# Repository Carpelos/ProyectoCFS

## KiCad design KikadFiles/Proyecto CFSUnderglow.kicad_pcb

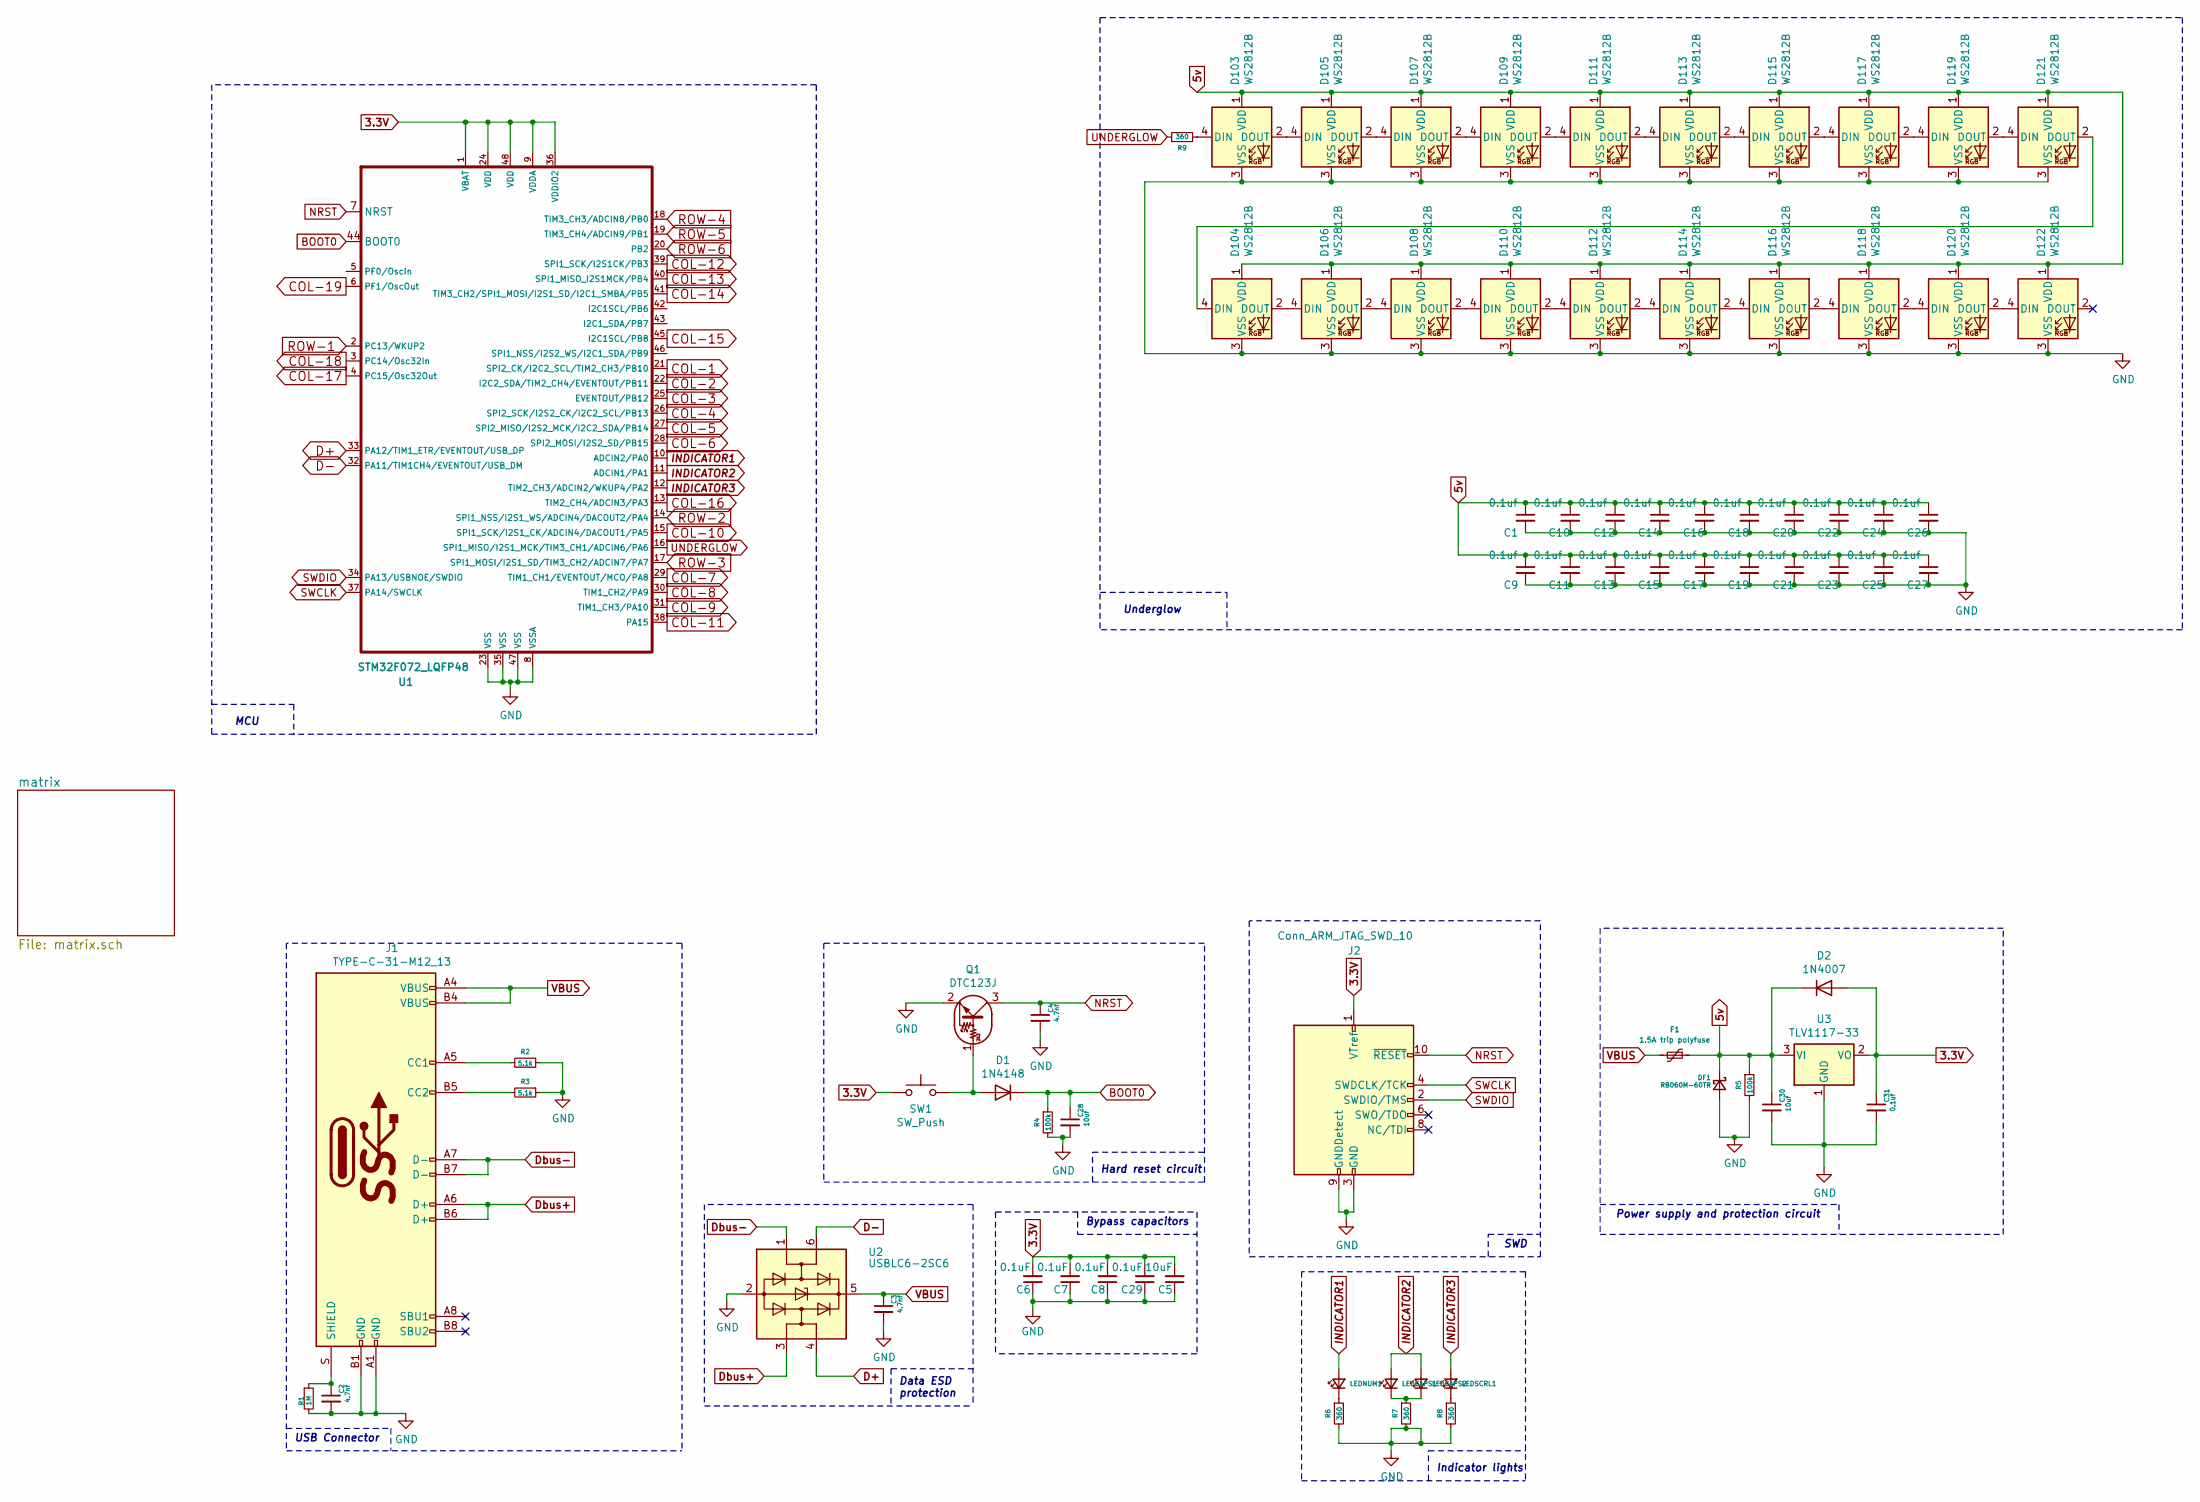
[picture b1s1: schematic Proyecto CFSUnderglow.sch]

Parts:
C1, C9, C10, C11, C12, C13, C14, C15, C16, C17, C18, C19, C20, C21, C22, C23, C24, C25, C26, C27, C31: 0.1uf; C_0805_2012Metric_Pad1.15x1.40mm_HandSolder
C2, C3, C4: 4.7nf; C_0805_2012Metric_Pad1.15x1.40mm_HandSolder
C5: 10uF; C_0805_2012Metric_Pad1.15x1.40mm_HandSolder
C6, C7, C8, C29: 0.1uF; C_0805_2012Metric_Pad1.15x1.40mm_HandSolder
C28, C30: 10uf; C_0805_2012Metric_Pad1.15x1.40mm_HandSolder
D1: 1N4148; D_SOD-123
D2: 1N4007; D_SOD-123
D103, D104, D105, D106, D107, D108, D109, D110, D111, D112, D113, D114, D115, D116, D117, D118, D119, D120, D121, D122: WS2812B; LED_WS2812B_PLCC4_5.0x5.0mm_P3.2mm
DF1: RB060M-60TR; D_SOD-123
F1: 1.5A trip polyfuse; Fuse_1812_4532Metric_Pad1.30x3.40mm_HandSolder
J1: TYPE-C-31-M12_13; TYPE-C-31-M-12
J2: Conn_ARM_JTAG_SWD_10; PinHeader_2x05_P2.54mm_Vertical
LEDCAPS1, LEDCAPS2: L; LED_D1.8mm_W3.3mm_H2.4mm
LEDNUM1: L; LED_D1.8mm_W3.3mm_H2.4mm
LEDSCRL1: L; LED_D1.8mm_W3.3mm_H2.4mm
Q1: DTC123J; SOT-23
R1: 1M; R_0805_2012Metric_Pad1.15x1.40mm_HandSolder
R2, R3: 5.1k; R_0805_2012Metric_Pad1.15x1.40mm_HandSolder
R4, R5: 100k; R_0805_2012Metric_Pad1.15x1.40mm_HandSolder
R6, R7, R8, R9: 360; R_0805_2012Metric_Pad1.15x1.40mm_HandSolder
SW1: SW_Push; smdPushBtn
U1: STM32F072_LQFP48; LQFP-48_7x7mm_P0.5mm
U2: USBLC6-2SC6; SOT-23-6
U3: TLV1117-33; SOT-223-3_TabPin2

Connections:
3.3V: C5.2, C6.2, C7.2, C8.2, C29.2, C31.1, D2.2 (A), J2.1 (VTref), SW1.1, U1.1 (VBAT), U1.9 (VDDA), U1.24 (VDD), U1.36 (VDDIO2), U1.48 (VDD), U3.2 (VO)
5v: C1.1, C9.1, C10.1, C11.1, C12.1, C13.1, C14.1, C15.1, C16.1, C17.1, C18.1, C19.1, C20.1, C21.1, C22.1, C23.1, C24.1, C25.1, C26.1, C27.1, C30.1, D2.1 (K), D103.1 (VDD), D104.1 (VDD), D105.1 (VDD), D106.1 (VDD), D107.1 (VDD), D108.1 (VDD), D109.1 (VDD), D110.1 (VDD), D111.1 (VDD), D112.1 (VDD), D113.1 (VDD), D114.1 (VDD), D115.1 (VDD), D116.1 (VDD), D117.1 (VDD), D118.1 (VDD), D119.1 (VDD), D120.1 (VDD), D121.1 (VDD), D122.1 (VDD), DF1.1 (K), F1.1, R5.1, U3.3 (VI)
BOOT0: C28.1, D1.1 (K), R4.1, U1.44 (BOOT0)
COL-1: U1.21 (SPI2_CK/I2C2_SCL/TIM2_CH3/PB10); also elsewhere on the board
COL-2: U1.22 (I2C2_SDA/TIM2_CH4/EVENTOUT/PB11); also elsewhere on the board
COL-3: U1.25 (EVENTOUT/PB12); also elsewhere on the board
COL-4: U1.26 (SPI2_SCK/I2S2_CK/I2C2_SCL/PB13); also elsewhere on the board
COL-5: U1.27 (SPI2_MISO/I2S2_MCK/I2C2_SDA/PB14); also elsewhere on the board
COL-6: U1.28 (SPI2_MOSI/I2S2_SD/PB15); also elsewhere on the board
COL-7: U1.29 (TIM1_CH1/EVENTOUT/MCO/PA8); also elsewhere on the board
COL-8: U1.30 (TIM1_CH2/PA9); also elsewhere on the board
COL-9: U1.31 (TIM1_CH3/PA10); also elsewhere on the board
COL-10: U1.15 (SPI1_SCK/I2S1_CK/ADCIN4/DACOUT1/PA5); also elsewhere on the board
COL-11: U1.38 (PA15); also elsewhere on the board
COL-12: U1.39 (SPI1_SCK/I2S1CK/PB3); also elsewhere on the board
COL-13: U1.40 (SPI1_MISO_I2S1MCK/PB4); also elsewhere on the board
COL-14: U1.41 (TIM3_CH2/SPI1_MOSI/I2S1_SD/I2C1_SMBA/PB5); also elsewhere on the board
COL-15: U1.45 (I2C1SCL/PB8); also elsewhere on the board
COL-16: U1.13 (TIM2_CH4/ADCIN3/PA3); also elsewhere on the board
COL-17: U1.4 (PC15/Osc32Out); also elsewhere on the board
COL-18: U1.3 (PC14/Osc32In); also elsewhere on the board
COL-19: U1.6 (PF1/OscOut); also elsewhere on the board
D+: U1.33 (PA12/TIM1_ETR/EVENTOUT/USB_DP), U2.4 (I/O2)
D-: U1.32 (PA11/TIM1CH4/EVENTOUT/USB_DM), U2.6 (I/O1)
Dbus+: J1.A6 (D+), J1.B6 (D+), U2.3 (I/O2)
Dbus-: J1.A7 (D-), J1.B7 (D-), U2.1 (I/O1)
GND: C1.2, C2.2, C3.2, C4.2, C5.1, C6.1, C7.1, C8.1, C9.2, C10.2, C11.2, C12.2, C13.2, C14.2, C15.2, C16.2, C17.2, C18.2, C19.2, C20.2, C21.2, C22.2, C23.2, C24.2, C25.2, C26.2, C27.2, C28.2, C29.1, C30.2, C31.2, D103.3 (VSS), D104.3 (VSS), D105.3 (VSS), D106.3 (VSS), D107.3 (VSS), D108.3 (VSS), D109.3 (VSS), D110.3 (VSS), D111.3 (VSS), D112.3 (VSS), D113.3 (VSS), D114.3 (VSS), D115.3 (VSS), D116.3 (VSS), D117.3 (VSS), D118.3 (VSS), D119.3 (VSS), D120.3 (VSS), D121.3 (VSS), D122.3 (VSS), DF1.2 (A), J1.A1 (GND), J1.B1 (GND), J2.3 (GND), J2.5 (GND), J2.9 (GNDDetect), Q1.2 (E), R1.2, R2.1, R3.1, R4.2, R5.2, R6.2, R7.2, R8.2, U1.8 (VSSA), U1.23 (VSS), U1.35 (VSS), U1.47 (VSS), U2.2 (GND), U3.1 (GND)
INDICATOR1: LEDNUM1.2 (A), U1.10 (ADCIN2/PA0)
INDICATOR2: LEDCAPS1.2 (A), LEDCAPS2.2 (A), U1.11 (ADCIN1/PA1)
INDICATOR3: LEDSCRL1.2 (A), U1.12 (TIM2_CH3/ADCIN2/WKUP4/PA2)
NRST: C4.1, J2.10 (~RESET~), Q1.3 (C), U1.7 (NRST)
unnamed: C2.1, J1.S (SHIELD), R1.1
unnamed: D1.2 (A), Q1.1 (B), SW1.2
unnamed: D103.2 (DOUT), D105.4 (DIN)
unnamed: D103.4 (DIN), R9.2
unnamed: D104.2 (DOUT), D106.4 (DIN)
unnamed: D104.4 (DIN), D121.2 (DOUT)
unnamed: D105.2 (DOUT), D107.4 (DIN)
unnamed: D106.2 (DOUT), D108.4 (DIN)
unnamed: D107.2 (DOUT), D109.4 (DIN)
unnamed: D108.2 (DOUT), D110.4 (DIN)
unnamed: D109.2 (DOUT), D111.4 (DIN)
unnamed: D110.2 (DOUT), D112.4 (DIN)
unnamed: D111.2 (DOUT), D113.4 (DIN)
unnamed: D112.2 (DOUT), D114.4 (DIN)
unnamed: D113.2 (DOUT), D115.4 (DIN)
unnamed: D114.2 (DOUT), D116.4 (DIN)
unnamed: D115.2 (DOUT), D117.4 (DIN)
unnamed: D116.2 (DOUT), D118.4 (DIN)
unnamed: D117.2 (DOUT), D119.4 (DIN)
unnamed: D118.2 (DOUT), D120.4 (DIN)
unnamed: D119.2 (DOUT), D121.4 (DIN)
unnamed: D120.2 (DOUT), D122.4 (DIN)
unnamed: J1.A5 (CC1), R2.2
unnamed: J1.B5 (CC2), R3.2
unnamed: LEDCAPS1.1 (K), LEDCAPS2.1 (K), R7.1
unnamed: LEDNUM1.1 (K), R6.1
unnamed: LEDSCRL1.1 (K), R8.1
ROW-1: U1.2 (PC13/WKUP2); also elsewhere on the board
ROW-2: U1.14 (SPI1_NSS/I2S1_WS/ADCIN4/DACOUT2/PA4); also elsewhere on the board
ROW-3: U1.17 (SPI1_MOSI/I2S1_SD/TIM3_CH2/ADCIN7/PA7); also elsewhere on the board
ROW-4: U1.18 (TIM3_CH3/ADCIN8/PB0); also elsewhere on the board
ROW-5: U1.19 (TIM3_CH4/ADCIN9/PB1); also elsewhere on the board
ROW-6: U1.20 (PB2); also elsewhere on the board
SWCLK: J2.4 (SWDCLK/TCK), U1.37 (PA14/SWCLK)
SWDIO: J2.2 (SWDIO/TMS), U1.34 (PA13/USBNOE/SWDIO)
UNDERGLOW: R9.1, U1.16 (SPI1_MISO/I2S1_MCK/TIM3_CH1/ADCIN6/PA6)
VBUS: C3.1, F1.2, J1.A4 (VBUS), J1.B4 (VBUS), U2.5 (VBUS)

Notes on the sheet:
USB Connector
Data ESD protection
Hard reset circuit
SWD
Bypass capacitors
Indicator lights
Power supply and protection circuit
Underglow
MCU

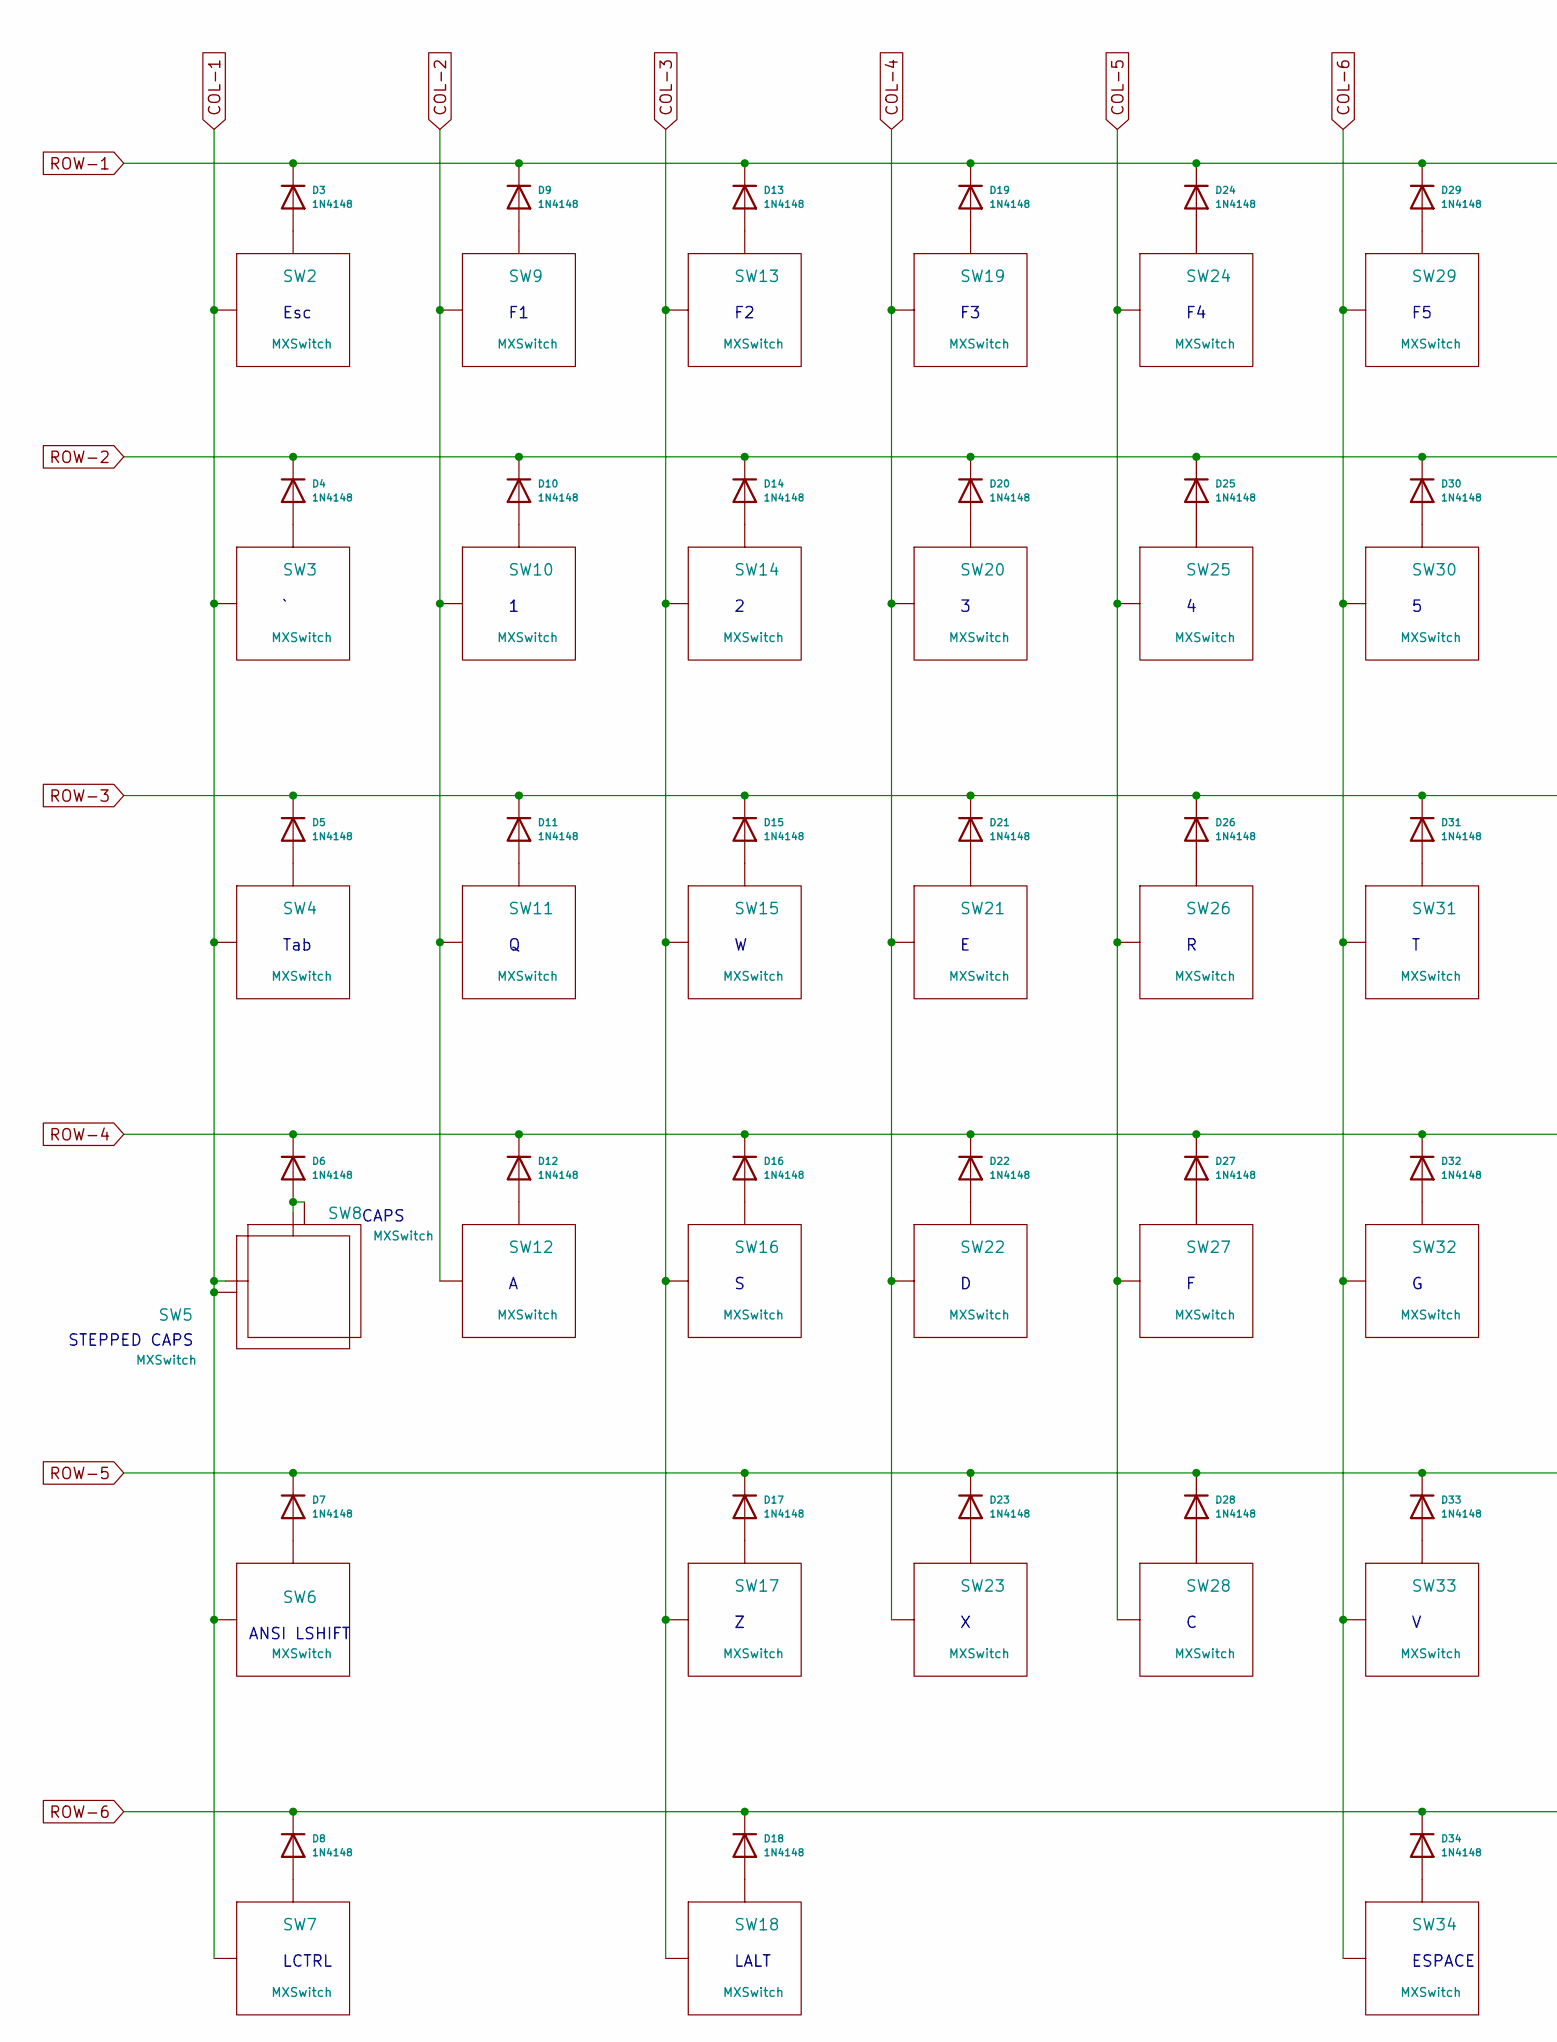
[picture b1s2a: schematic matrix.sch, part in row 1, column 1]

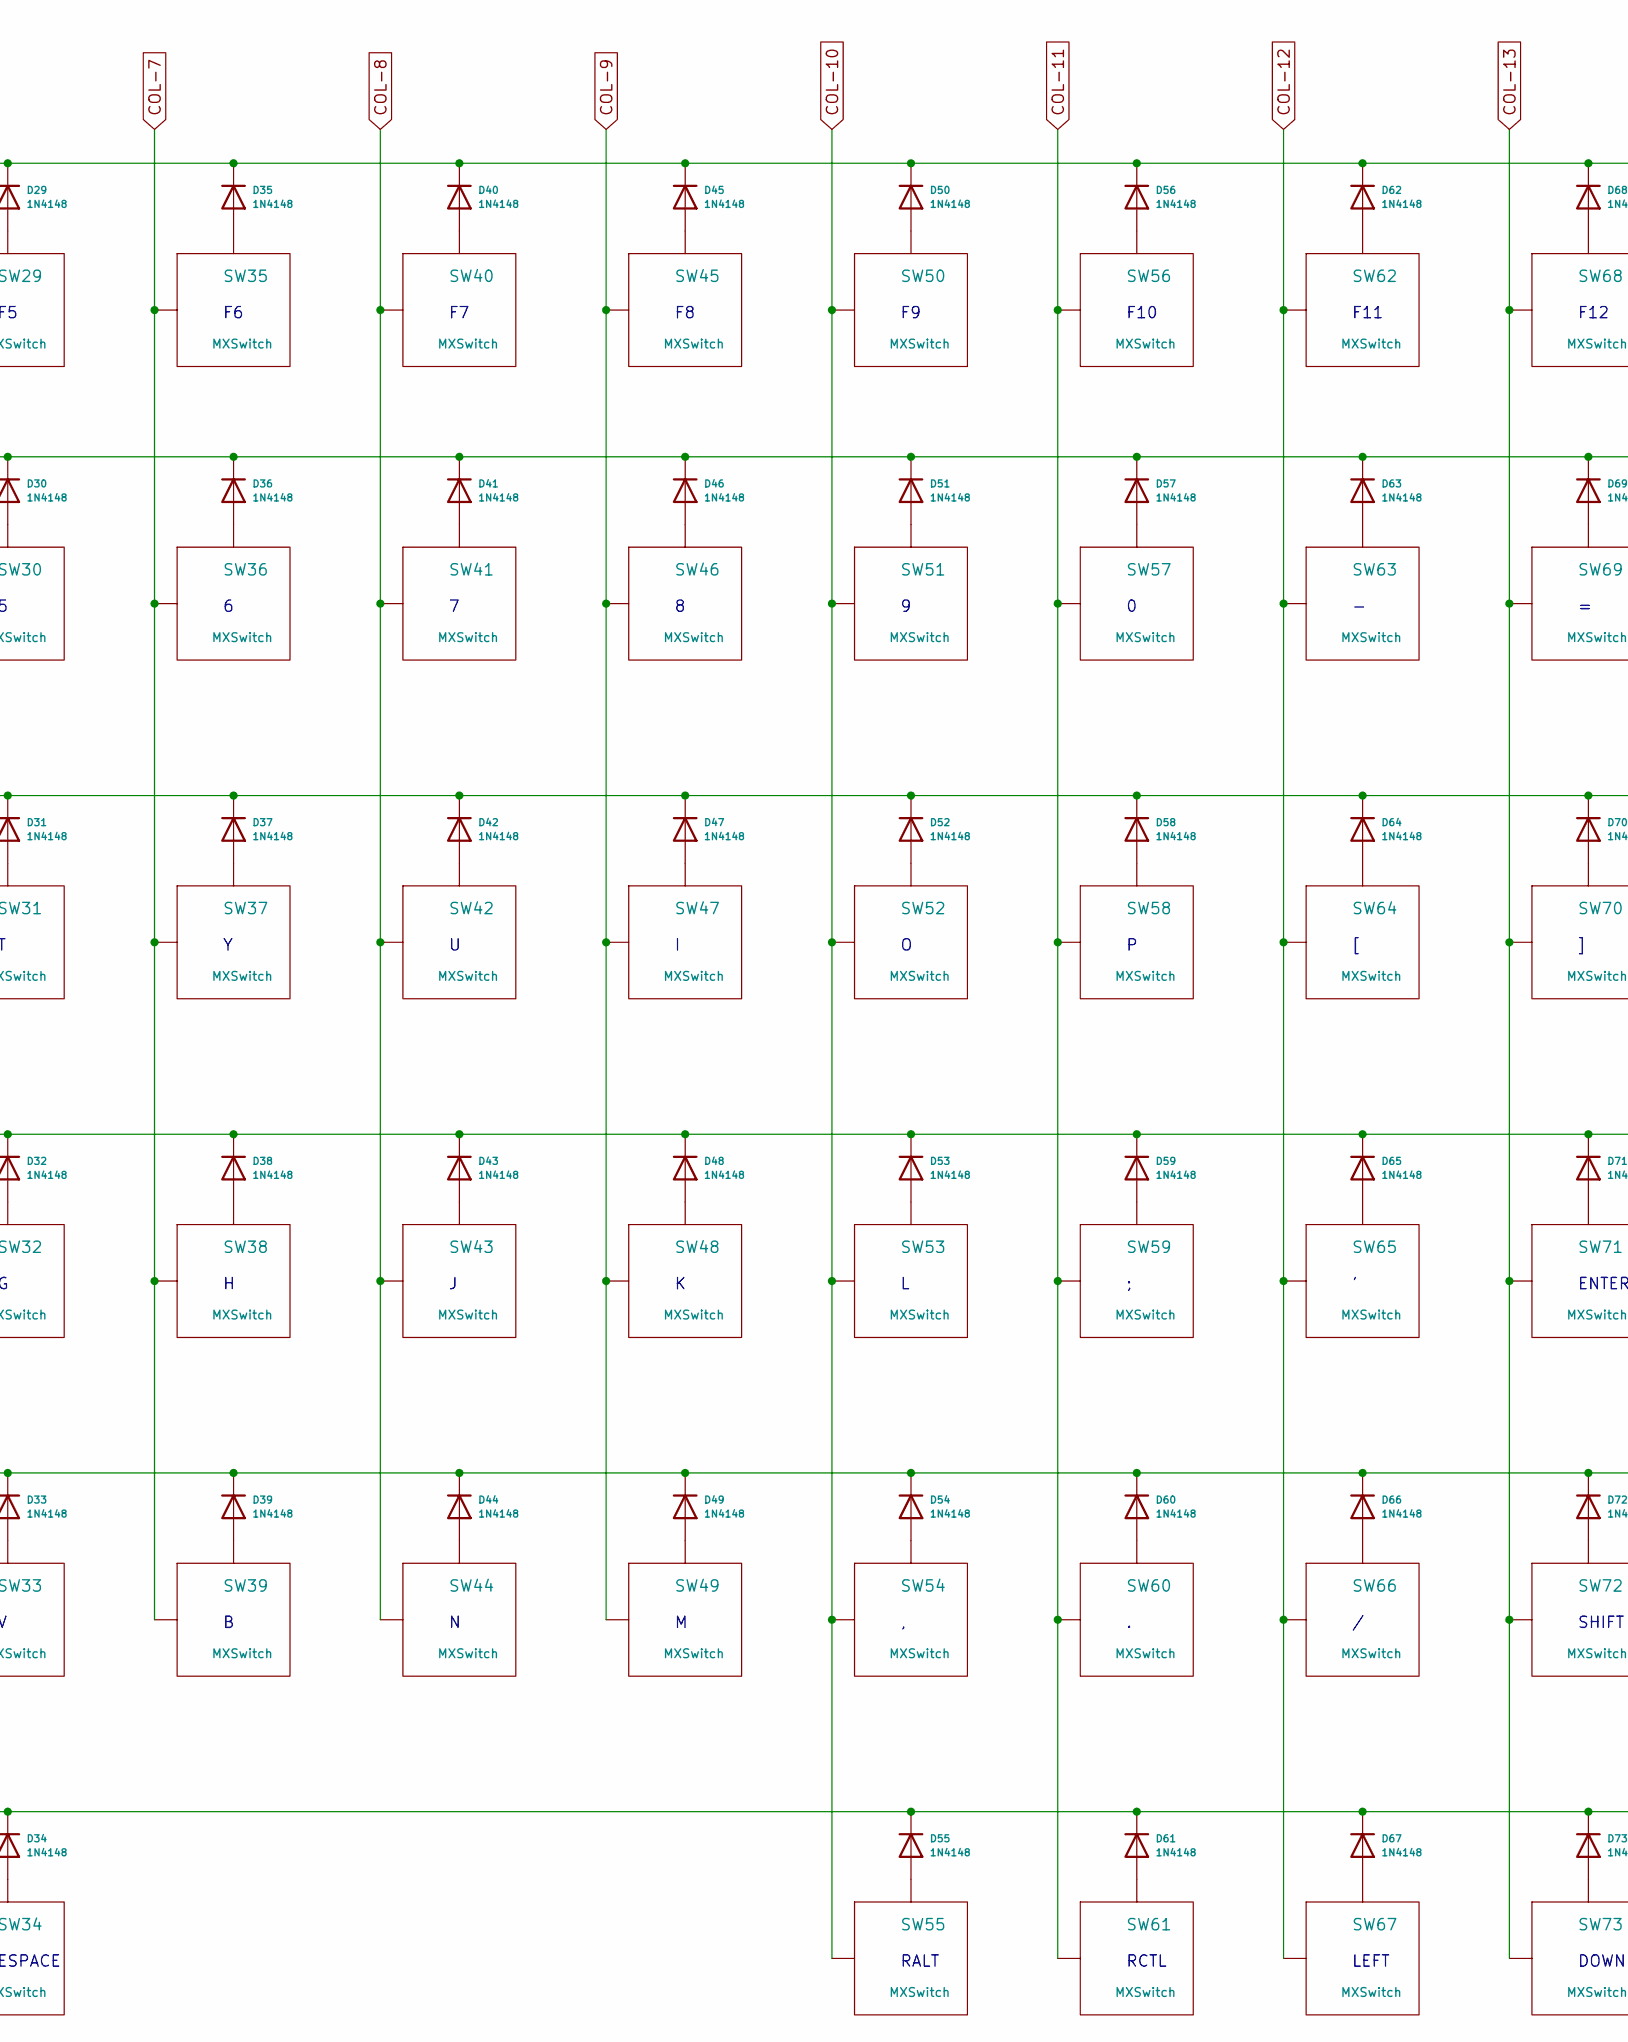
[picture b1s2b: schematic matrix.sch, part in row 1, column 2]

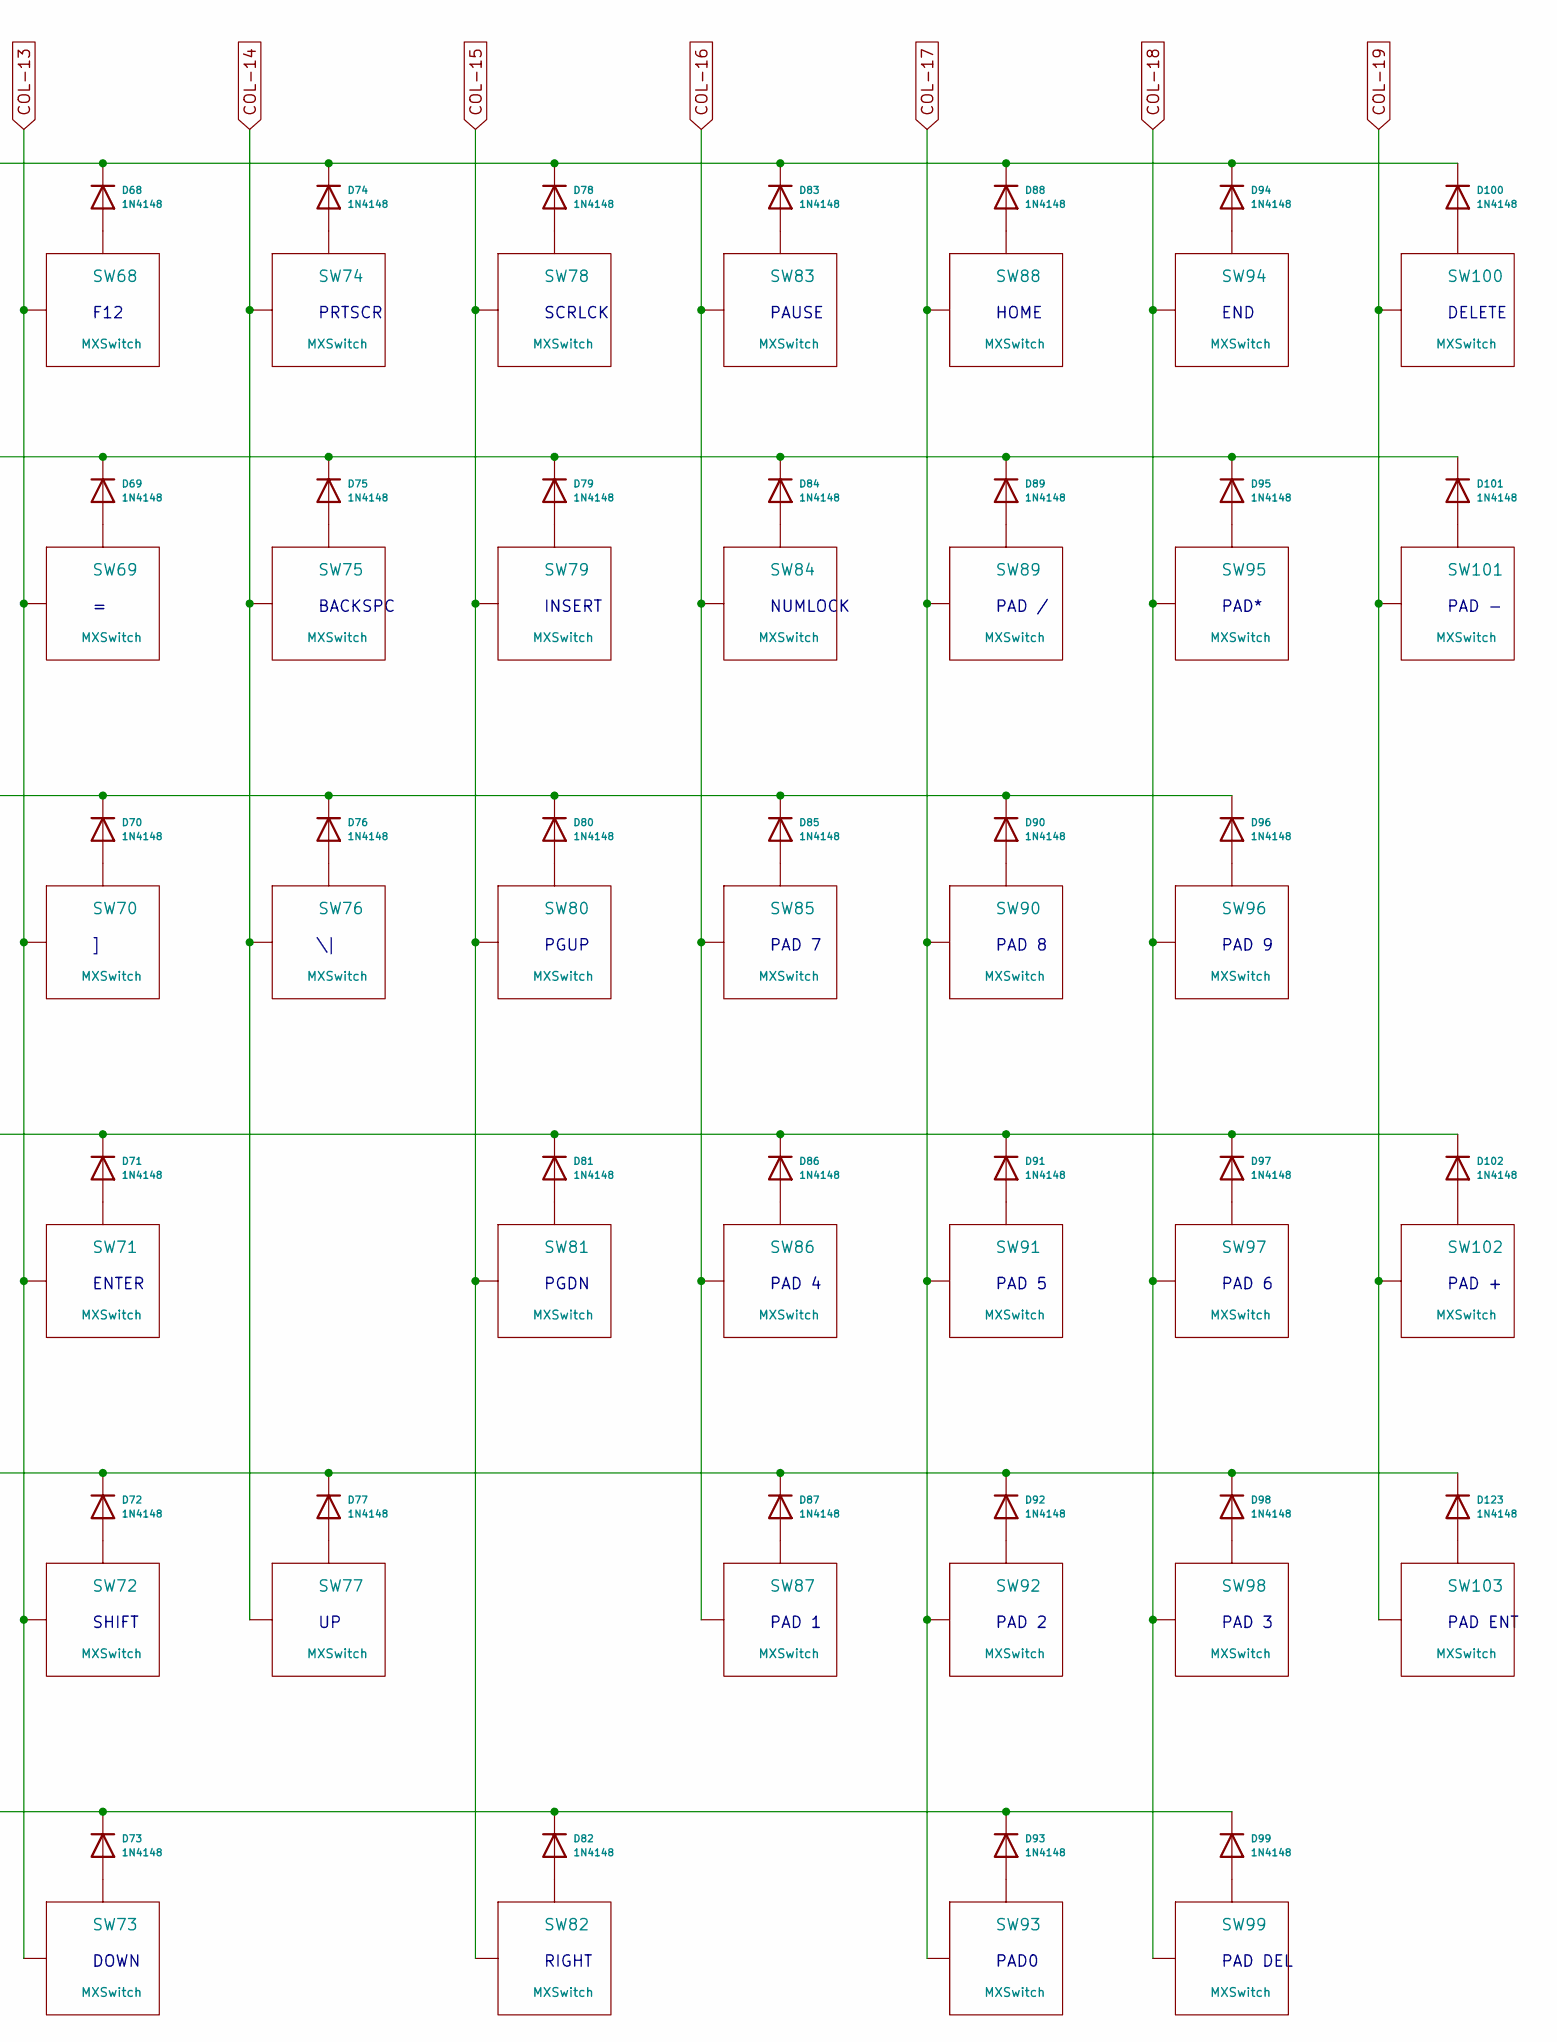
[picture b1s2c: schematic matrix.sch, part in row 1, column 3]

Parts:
D3, D4, D5, D6, D7, D8, D9, D10, D11, D12, D13, D14, D15, D16, D17, D18, D19, D20, D21, D22, D23, D24, D25, D26, D27, D28, D29, D30, D31, D32, D33, D34, D35, D36, D37, D38, D39, D40, D41, D42, D43, D44, D45, D46, D47, D48, D49, D50, D51, D52, D53, D54, D55, D56, D57, D58, D59, D60, D61, D62, D63, D64, D65, D66, D67, D68, D69, D70, D71, D72, D73, D74, D75, D76, D77, D78, D79, D80, D81, D82, D83, D84, D85, D86, D87, D88, D89, D90, D91, D92, D93, D94, D95, D96, D97, D98, D99, D100, D101, D102, D123: 1N4148; D_SOD-123
SW2, SW3, SW9, SW10, SW11, SW12, SW13, SW14, SW15, SW16, SW17, SW19, SW20, SW21, SW22, SW23, SW24, SW25, SW26, SW27, SW28, SW29, SW30, SW31, SW32, SW33, SW35, SW36, SW37, SW38, SW39, SW40, SW41, SW42, SW43, SW44, SW45, SW46, SW47, SW48, SW49, SW50, SW51, SW52, SW53, SW54, SW56, SW57, SW58, SW59, SW60, SW62, SW63, SW64, SW65, SW66, SW67, SW68, SW69, SW70, SW73, SW74, SW77, SW78, SW79, SW80, SW81, SW82, SW83, SW84, SW85, SW86, SW87, SW88, SW89, SW90, SW91, SW92, SW94, SW95, SW96, SW97, SW98, SW99, SW100, SW101: MXSwitch; MXOnly-1U-NoLED
SW4, SW7, SW18, SW55, SW61, SW76: MXSwitch; MXOnly-1.5U-NoLED
SW5: MXSwitch; MXOnly-1.25U-NoLED
SW6, SW71: MXSwitch; MXOnly-2.25U-NoLED
SW8, SW72: MXSwitch; MXOnly-1.75U-NoLED
SW34: MXSwitch; MXOnly-7U-NoLED
SW75, SW93, SW102, SW103: MXSwitch; MXOnly-2U-NoLED

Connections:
COL-1: SW2.1 (Col), SW3.1 (Col), SW4.1 (Col), SW5.1 (Col), SW6.1 (Col), SW7.1 (Col), SW8.1 (Col); also elsewhere on the board
COL-2: SW9.1 (Col), SW10.1 (Col), SW11.1 (Col), SW12.1 (Col); also elsewhere on the board
COL-3: SW13.1 (Col), SW14.1 (Col), SW15.1 (Col), SW16.1 (Col), SW17.1 (Col), SW18.1 (Col); also elsewhere on the board
COL-4: SW19.1 (Col), SW20.1 (Col), SW21.1 (Col), SW22.1 (Col), SW23.1 (Col); also elsewhere on the board
COL-5: SW24.1 (Col), SW25.1 (Col), SW26.1 (Col), SW27.1 (Col), SW28.1 (Col); also elsewhere on the board
COL-6: SW29.1 (Col), SW30.1 (Col), SW31.1 (Col), SW32.1 (Col), SW33.1 (Col), SW34.1 (Col); also elsewhere on the board
COL-7: SW35.1 (Col), SW36.1 (Col), SW37.1 (Col), SW38.1 (Col), SW39.1 (Col); also elsewhere on the board
COL-8: SW40.1 (Col), SW41.1 (Col), SW42.1 (Col), SW43.1 (Col), SW44.1 (Col); also elsewhere on the board
COL-9: SW45.1 (Col), SW46.1 (Col), SW47.1 (Col), SW48.1 (Col), SW49.1 (Col); also elsewhere on the board
COL-10: SW50.1 (Col), SW51.1 (Col), SW52.1 (Col), SW53.1 (Col), SW54.1 (Col), SW55.1 (Col); also elsewhere on the board
COL-11: SW56.1 (Col), SW57.1 (Col), SW58.1 (Col), SW59.1 (Col), SW60.1 (Col), SW61.1 (Col); also elsewhere on the board
COL-12: SW62.1 (Col), SW63.1 (Col), SW64.1 (Col), SW65.1 (Col), SW66.1 (Col), SW67.1 (Col); also elsewhere on the board
COL-13: SW68.1 (Col), SW69.1 (Col), SW70.1 (Col), SW71.1 (Col), SW72.1 (Col), SW73.1 (Col); also elsewhere on the board
COL-14: SW74.1 (Col), SW75.1 (Col), SW76.1 (Col), SW77.1 (Col); also elsewhere on the board
COL-15: SW78.1 (Col), SW79.1 (Col), SW80.1 (Col), SW81.1 (Col), SW82.1 (Col); also elsewhere on the board
COL-16: SW83.1 (Col), SW84.1 (Col), SW85.1 (Col), SW86.1 (Col), SW87.1 (Col); also elsewhere on the board
COL-17: SW88.1 (Col), SW89.1 (Col), SW90.1 (Col), SW91.1 (Col), SW92.1 (Col), SW93.1 (Col); also elsewhere on the board
COL-18: SW94.1 (Col), SW95.1 (Col), SW96.1 (Col), SW97.1 (Col), SW98.1 (Col), SW99.1 (Col); also elsewhere on the board
COL-19: SW100.1 (Col), SW101.1 (Col), SW102.1 (Col), SW103.1 (Col); also elsewhere on the board
unnamed: D3.2 (A), SW2.2 (Row)
unnamed: D4.2 (A), SW3.2 (Row)
unnamed: D5.2 (A), SW4.2 (Row)
unnamed: D6.2 (A), SW5.2 (Row), SW8.2 (Row)
unnamed: D7.2 (A), SW6.2 (Row)
unnamed: D8.2 (A), SW7.2 (Row)
unnamed: D9.2 (A), SW9.2 (Row)
unnamed: D10.2 (A), SW10.2 (Row)
unnamed: D11.2 (A), SW11.2 (Row)
unnamed: D12.2 (A), SW12.2 (Row)
unnamed: D13.2 (A), SW13.2 (Row)
unnamed: D14.2 (A), SW14.2 (Row)
unnamed: D15.2 (A), SW15.2 (Row)
unnamed: D16.2 (A), SW16.2 (Row)
unnamed: D17.2 (A), SW17.2 (Row)
unnamed: D18.2 (A), SW18.2 (Row)
unnamed: D19.2 (A), SW19.2 (Row)
unnamed: D20.2 (A), SW20.2 (Row)
unnamed: D21.2 (A), SW21.2 (Row)
unnamed: D22.2 (A), SW22.2 (Row)
unnamed: D23.2 (A), SW23.2 (Row)
unnamed: D24.2 (A), SW24.2 (Row)
unnamed: D25.2 (A), SW25.2 (Row)
unnamed: D26.2 (A), SW26.2 (Row)
unnamed: D27.2 (A), SW27.2 (Row)
unnamed: D28.2 (A), SW28.2 (Row)
unnamed: D29.2 (A), SW29.2 (Row)
unnamed: D30.2 (A), SW30.2 (Row)
unnamed: D31.2 (A), SW31.2 (Row)
unnamed: D32.2 (A), SW32.2 (Row)
unnamed: D33.2 (A), SW33.2 (Row)
unnamed: D34.2 (A), SW34.2 (Row)
unnamed: D35.2 (A), SW35.2 (Row)
unnamed: D36.2 (A), SW36.2 (Row)
unnamed: D37.2 (A), SW37.2 (Row)
unnamed: D38.2 (A), SW38.2 (Row)
unnamed: D39.2 (A), SW39.2 (Row)
unnamed: D40.2 (A), SW40.2 (Row)
unnamed: D41.2 (A), SW41.2 (Row)
unnamed: D42.2 (A), SW42.2 (Row)
unnamed: D43.2 (A), SW43.2 (Row)
unnamed: D44.2 (A), SW44.2 (Row)
unnamed: D45.2 (A), SW45.2 (Row)
unnamed: D46.2 (A), SW46.2 (Row)
unnamed: D47.2 (A), SW47.2 (Row)
unnamed: D48.2 (A), SW48.2 (Row)
unnamed: D49.2 (A), SW49.2 (Row)
unnamed: D50.2 (A), SW50.2 (Row)
unnamed: D51.2 (A), SW51.2 (Row)
unnamed: D52.2 (A), SW52.2 (Row)
unnamed: D53.2 (A), SW53.2 (Row)
unnamed: D54.2 (A), SW54.2 (Row)
unnamed: D55.2 (A), SW55.2 (Row)
unnamed: D56.2 (A), SW56.2 (Row)
unnamed: D57.2 (A), SW57.2 (Row)
unnamed: D58.2 (A), SW58.2 (Row)
unnamed: D59.2 (A), SW59.2 (Row)
unnamed: D60.2 (A), SW60.2 (Row)
unnamed: D61.2 (A), SW61.2 (Row)
unnamed: D62.2 (A), SW62.2 (Row)
unnamed: D63.2 (A), SW63.2 (Row)
unnamed: D64.2 (A), SW64.2 (Row)
unnamed: D65.2 (A), SW65.2 (Row)
unnamed: D66.2 (A), SW66.2 (Row)
unnamed: D67.2 (A), SW67.2 (Row)
unnamed: D68.2 (A), SW68.2 (Row)
unnamed: D69.2 (A), SW69.2 (Row)
unnamed: D70.2 (A), SW70.2 (Row)
unnamed: D71.2 (A), SW71.2 (Row)
unnamed: D72.2 (A), SW72.2 (Row)
unnamed: D73.2 (A), SW73.2 (Row)
unnamed: D74.2 (A), SW74.2 (Row)
unnamed: D75.2 (A), SW75.2 (Row)
unnamed: D76.2 (A), SW76.2 (Row)
unnamed: D77.2 (A), SW77.2 (Row)
unnamed: D78.2 (A), SW78.2 (Row)
unnamed: D79.2 (A), SW79.2 (Row)
unnamed: D80.2 (A), SW80.2 (Row)
unnamed: D81.2 (A), SW81.2 (Row)
unnamed: D82.2 (A), SW82.2 (Row)
unnamed: D83.2 (A), SW83.2 (Row)
unnamed: D84.2 (A), SW84.2 (Row)
unnamed: D85.2 (A), SW85.2 (Row)
unnamed: D86.2 (A), SW86.2 (Row)
unnamed: D87.2 (A), SW87.2 (Row)
unnamed: D88.2 (A), SW88.2 (Row)
unnamed: D89.2 (A), SW89.2 (Row)
unnamed: D90.2 (A), SW90.2 (Row)
unnamed: D91.2 (A), SW91.2 (Row)
unnamed: D92.2 (A), SW92.2 (Row)
unnamed: D93.2 (A), SW93.2 (Row)
unnamed: D94.2 (A), SW94.2 (Row)
unnamed: D95.2 (A), SW95.2 (Row)
unnamed: D96.2 (A), SW96.2 (Row)
unnamed: D97.2 (A), SW97.2 (Row)
unnamed: D98.2 (A), SW98.2 (Row)
unnamed: D99.2 (A), SW99.2 (Row)
unnamed: D100.2 (A), SW100.2 (Row)
unnamed: D101.2 (A), SW101.2 (Row)
unnamed: D102.2 (A), SW102.2 (Row)
unnamed: D123.2 (A), SW103.2 (Row)
ROW-1: D3.1 (K), D9.1 (K), D13.1 (K), D19.1 (K), D24.1 (K), D29.1 (K), D35.1 (K), D40.1 (K), D45.1 (K), D50.1 (K), D56.1 (K), D62.1 (K), D68.1 (K), D74.1 (K), D78.1 (K), D83.1 (K), D88.1 (K), D94.1 (K), D100.1 (K); also elsewhere on the board
ROW-2: D4.1 (K), D10.1 (K), D14.1 (K), D20.1 (K), D25.1 (K), D30.1 (K), D36.1 (K), D41.1 (K), D46.1 (K), D51.1 (K), D57.1 (K), D63.1 (K), D69.1 (K), D75.1 (K), D79.1 (K), D84.1 (K), D89.1 (K), D95.1 (K), D101.1 (K); also elsewhere on the board
ROW-3: D5.1 (K), D11.1 (K), D15.1 (K), D21.1 (K), D26.1 (K), D31.1 (K), D37.1 (K), D42.1 (K), D47.1 (K), D52.1 (K), D58.1 (K), D64.1 (K), D70.1 (K), D76.1 (K), D80.1 (K), D85.1 (K), D90.1 (K), D96.1 (K); also elsewhere on the board
ROW-4: D6.1 (K), D12.1 (K), D16.1 (K), D22.1 (K), D27.1 (K), D32.1 (K), D38.1 (K), D43.1 (K), D48.1 (K), D53.1 (K), D59.1 (K), D65.1 (K), D71.1 (K), D81.1 (K), D86.1 (K), D91.1 (K), D97.1 (K), D102.1 (K); also elsewhere on the board
ROW-5: D7.1 (K), D17.1 (K), D23.1 (K), D28.1 (K), D33.1 (K), D39.1 (K), D44.1 (K), D49.1 (K), D54.1 (K), D60.1 (K), D66.1 (K), D72.1 (K), D77.1 (K), D87.1 (K), D92.1 (K), D98.1 (K), D123.1 (K); also elsewhere on the board
ROW-6: D8.1 (K), D18.1 (K), D34.1 (K), D55.1 (K), D61.1 (K), D67.1 (K), D73.1 (K), D82.1 (K), D93.1 (K), D99.1 (K); also elsewhere on the board

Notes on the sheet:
Esc
F10
F11
F12
PRTSCR
SCRLCK
PAUSE
HOME
END
DELETE
BACKSPC
INSERT
NUMLOCK
PAD /
PAD*
Tab
PGUP
PAD 7
PAD 8
PAD 9
CAPS
ENTER
PGDN
PAD 4
PAD 5
PAD 6
PAD +
ANSI LSHIFT
SHIFT
PAD 1
PAD 2
PAD 3
PAD ENT
LCTRL
LALT
ESPACE
RALT
RCTL
LEFT
DOWN

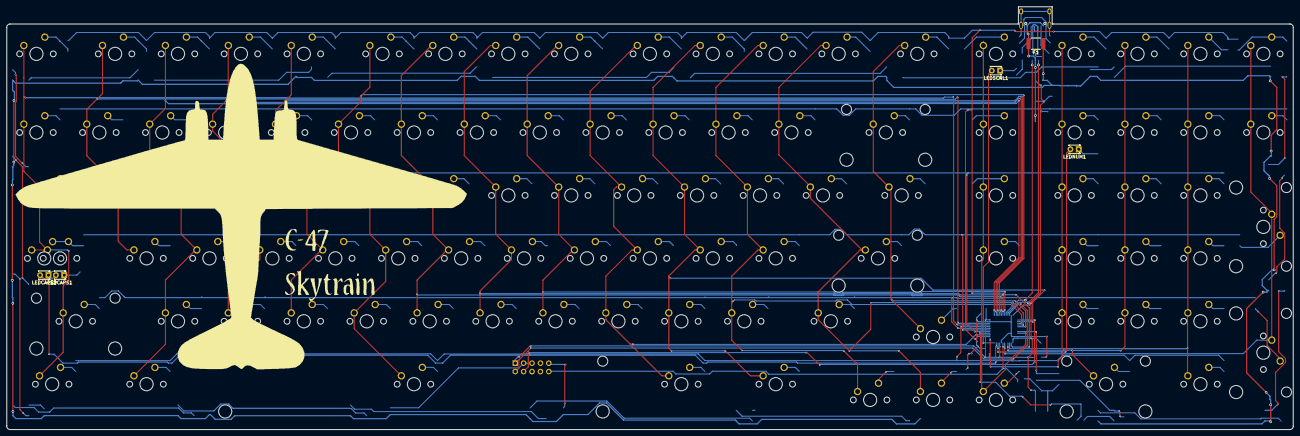
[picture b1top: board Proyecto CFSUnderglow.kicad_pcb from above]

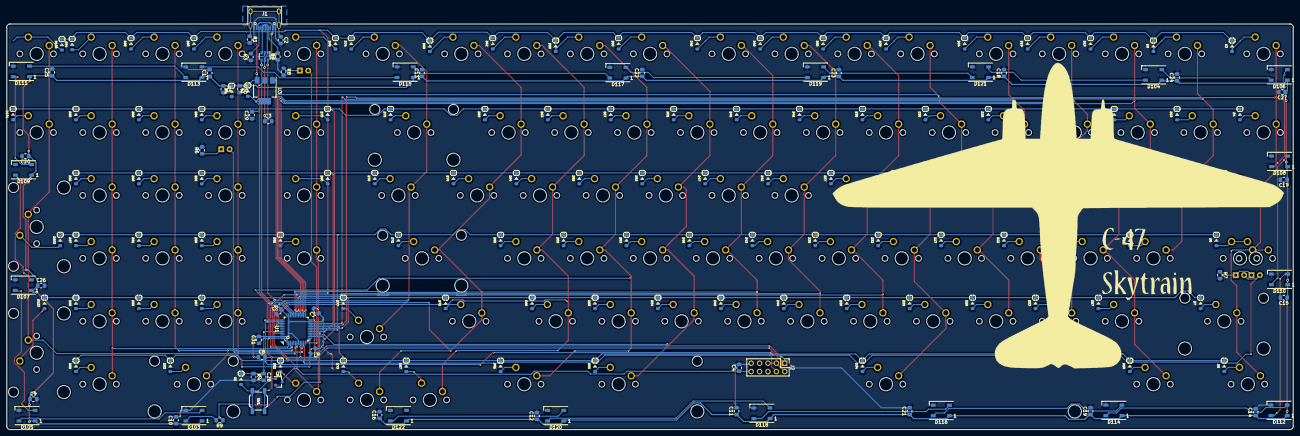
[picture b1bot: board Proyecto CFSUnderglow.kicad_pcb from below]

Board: 2 copper layers, 389.5 x 128.0 mm, 278 parts (171 on the bottom side), 169 nets.

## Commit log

2020-08-05 Readme
    Under development
2020-08-29 Caja acrílica, firmware qmk
